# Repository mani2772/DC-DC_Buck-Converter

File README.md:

# DC-DC_BUCK-CONVERTER-PCB
DC-DC BUCK CONVERTER using **LM2596T-12**. Designed in **KiCad**.

---

## 📌 Overview
This project implements a **DC-DC BUCK CONVERTER** based on the **LM2596T-12** regulator.  
It is designed in **KiCad** with the following specifications:  
- Input Voltage: 12–36 V DC  
- Output Voltage: 12 V DC, 1 A  
- Input protection: 1 A fuse, SS14 Schottky diode (reverse polarity protection)  
- Output indicators: LED with series resistor  
- Capacitors: Electrolytic + ceramic for filtering  
- Adjustable output via trim-pot for fine voltage tuning  

---

## 📂 Repository Structure
- `Source_files_DC-DC_Buck-Converter/Schematics/` → KiCad schematic files (`.kicad_sch`, `.kicad_pro`)  
- `ource_files_DC-DC_Buck-Converter/Schematics/PCB/` → PCB layout file (`.kicad_pcb`)  

---

## 📷 Design Media

### 🔹3D-Model

### 🔹Front-CU View

### 🔹Back-CU View

---

## 🛠 Tools Used
- **KiCad 9** → Schematic & PCB design  
- **GitHub** → Version control & project hosting  

---

DUNNA MANIKANTA  
bt22ece104@iiitn.ac.in

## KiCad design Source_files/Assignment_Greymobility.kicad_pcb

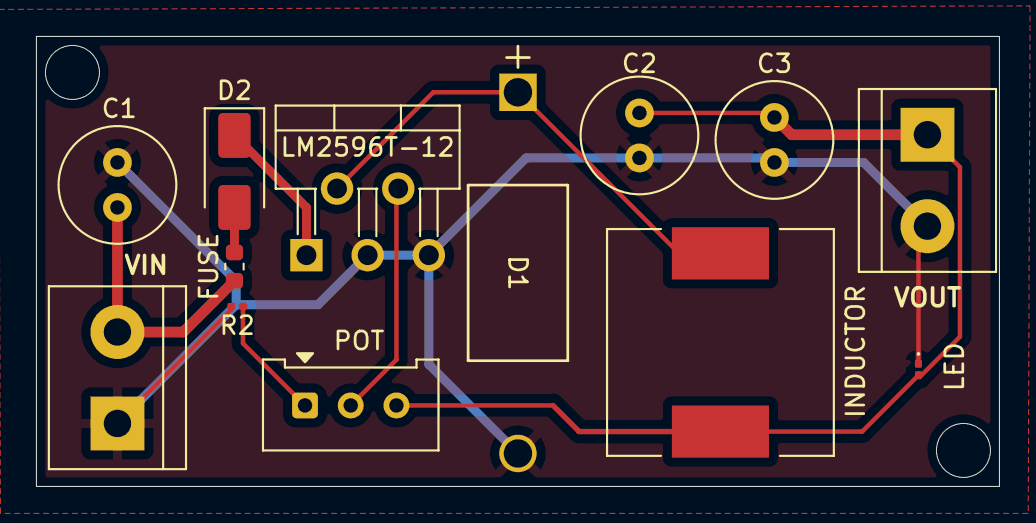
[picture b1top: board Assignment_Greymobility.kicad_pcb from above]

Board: 2 copper layers, 53.5 x 25.0 mm, 13 parts (0 on the bottom side), 8 nets.

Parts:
C1, C2: 100uF; C_Radial_D6.3mm_H11.0mm_P2.50mm
C3: 220uF; C_Radial_D6.3mm_H11.0mm_P2.50mm
D1: 1N5822; DIODE_1N5822-T_DIO
D2: SS14; D_SMA
FUSE: Fuse; Fuse_0603_1608Metric
INDUCTOR: 33uH; L_12x12mm_H8mm
LED: LED; LED_0201_0603Metric
LM2596T-12: LM2596T-12; TO-220-5_P3.4x3.7mm_StaggerOdd_Lead3.8mm_Vertical
POT: 50k; Potentiometer_Bourns_3386W_Horizontal
R2: 1.21k; R_0201_0603Metric
VIN: Screw_Terminal_01x02; TerminalBlock_bornier-2_P5.08mm
VOUT: Screw_Terminal_01x02; TerminalBlock_bornier-2_P5.08mm

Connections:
GNDREF: C1.2, C2.2, C3.2, D1.2 (A), LED.1 (K), LM2596T-12.3 (GND), LM2596T-12.5 (~ON/OFF), R2.2, VIN.1, VOUT.2
unnamed: D1.1 (K), INDUCTOR.1, LM2596T-12.2 (OUT)
unnamed: D2.2 (A), FUSE.2
unnamed: D2.1 (K), LM2596T-12.1 (VIN)
unnamed: C2.1, C3.1, INDUCTOR.2, LED.2 (A), POT.3, VOUT.1
unnamed: C1.1, FUSE.1, VIN.2
unnamed: POT.1, R2.1
unnamed: LM2596T-12.4 (FB), POT.2

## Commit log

2025-10-07 README.md
